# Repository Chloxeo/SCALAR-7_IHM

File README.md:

# SCALAR-7 : IHM Bas

HMI (Human-Machine Interface) board of the **lower stage** of **SCALAR-7**, a two-stage rocket launched at **C'Space 2026**.
It is the external control panel of the lower stage: it switches on, arms and monitors the **sequencer** and the **experiment** boards, and gives access to their debug ports without opening the rocket.

---
## Table of contents

- [Board features](#board-features)
- [Architecture](#architecture)
  - [Sequencer side](#sequencer-side)
  - [Experiment side](#experiment-side)
- [Main components](#main-components)
- [Repository structure](#repository-structure)

---

## Board features

| Function | Sequencer side | Experiment side |
|---|---|---|
| Board connection | D-Sub 15 (J2) | D-Sub 15 (J5) |
| Power switch | SPDT switch on the battery line (SW3) | SPDT switch on the battery line (SW4) |
| Arming | Arming jack connector (J1) | Arming jack connector (J4) |
| Status LEDs | 3V3, 5V, 6V, 12V rails + sequencer status | 3V3, 5V rails + experiment status |
| Debug | 6-pin connector for the Pico (SWD, UART, debug supply) (J3) | 6-pin connector for the Pico (SWD, UART, debug supply) (J6) |
| Test buttons | Parachute servo (SW2) and SSIE motor (SW1) | — |

---

## Architecture

```mermaid
flowchart LR
    subgraph SEQ_SIDE[Sequencer side]
        SW3[Power switch] 
        J1[Arming jack]
        LEDS_SEQ[Rail + status LEDs]
        BTN[SSIE / parachute<br/>test buttons]
        DBG_SEQ[Debug connector]
    end
    subgraph EXP_SIDE[Experiment side]
        SW4[Power switch]
        J4[Arming jack]
        LEDS_EXP[Rail + status LEDs]
        DBG_EXP[Debug connector]
    end

    SEQ[Sequencer board] <-- D-Sub 15 --> SEQ_SIDE
    EXP[Experiment board] <-- D-Sub 15 --> EXP_SIDE
```

The board has no microcontroller: it only routes signals and power. It is split into two independent halves, each with its own ground (`GND_SEQ` and `GND_EXP`), so the sequencer and the experiment stay electrically separated.

### Sequencer side

- **Power**: the sequencer's battery comes onto the HMI through the D-Sub connector and goes back through the power switch, which switches the sequencer on.
- **Arming**: the arming jack connector sends its state to a GPIO of the sequencer's Pico.
- **Status**: one LED per supply rail (3V3, 5V, 6V, 12V) and one status LED driven by the sequencer.
- **Tests**: two push buttons trigger the SSIE motor and the parachute servo for ground tests.
- **Debug**: a 6-pin connector gives access to the Pico's SWD, debug UART and debug supply.

### Experiment side

- **Power**: same principle as the sequencer side, with its own power switch.
- **Arming**: the arming jack connector sends its state to a GPIO of the experiment board's Pico.
- **Status**: one LED per supply rail (3V3, 5V) and one status LED driven by the experiment board.
- **Debug**: a 6-pin connector gives access to the Pico's SWD, debug UART and debug supply.

---

## Main components

| Ref. | Component | Function |
|---|---|---|
| J2, J5 | D-Sub 15 | Connection to the sequencer / experiment boards |
| SW3, SW4 | SPDT switches | Power switches |
| J1, J4 | 2-pin connectors | Arming jacks |
| J3, J6 | 6-pin connectors | Pico debug |
| SW1, SW2 | TE 1825910-6 | SSIE and parachute test buttons |
| D1–D8 | LEDs | Rail and status indicators |

---

## Repository structure

```
SCALAR-7_IHM_Bas/
├── hardware/          # KiCad project
├── images/
├── schematic.pdf
└── README.md
```

---

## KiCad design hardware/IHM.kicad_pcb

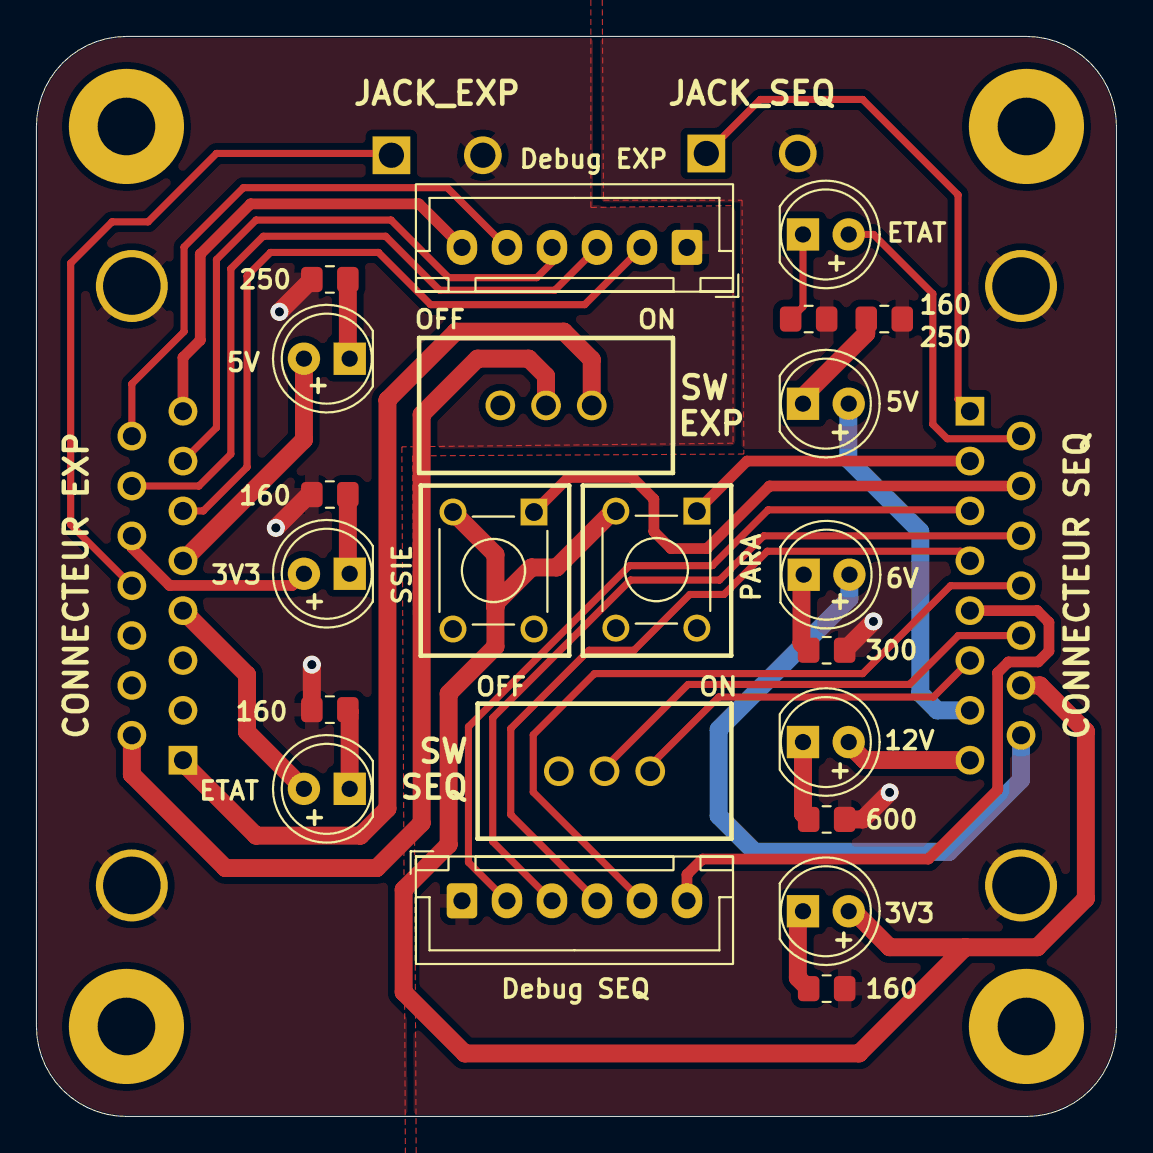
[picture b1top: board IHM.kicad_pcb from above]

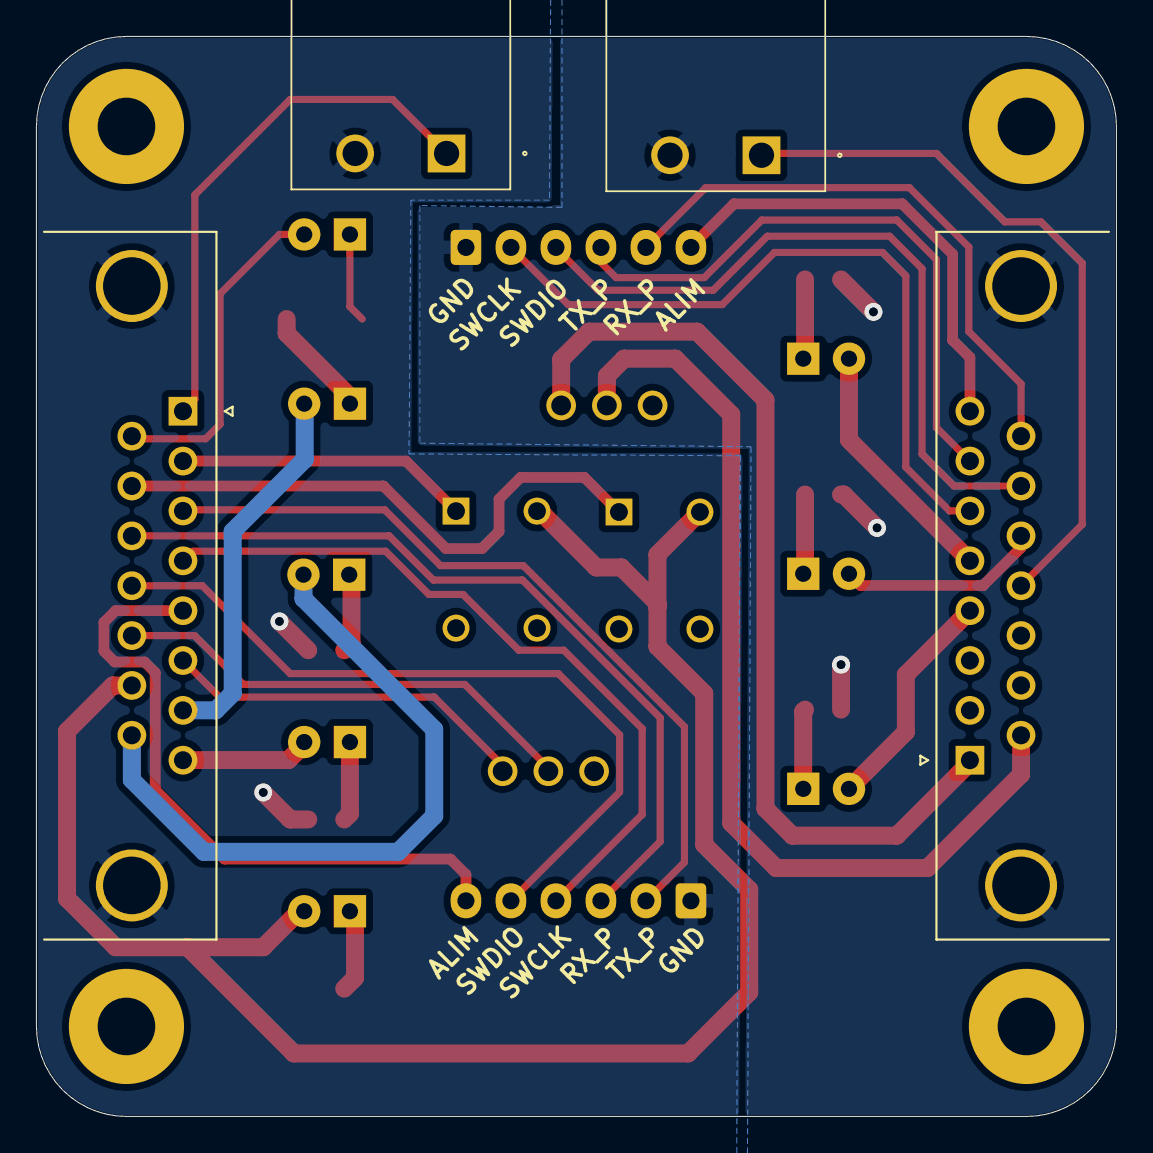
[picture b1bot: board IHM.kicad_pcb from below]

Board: 2 copper layers, 60.0 x 60.0 mm, 30 parts (4 on the bottom side), 36 nets.

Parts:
D1, D2, D3, D4, D5, D6, D7, D8: LED; LED_D5.0mm
H1, H2, H3, H4: MountingHole; MountingHole_3.2mm_M3_Pad
J1: JACK_SEQ; Bornier_Enfichable_2Pin_5mm_Horizontal
J2: CONNECTEUR SEQ; DSUB-15_Pins_Horizontal_P2.77x2.84mm_EdgePinOffset4.94mm_Ho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
J3: Debug SEQ; JST_XH_B6B-XH-A_1x06_P2.50mm_Vertical
J4: JACK_EXP; Bornier_Enfichable_2Pin_5mm_Horizontal
J5: CONNECTEUR EXP; DSUB-15_Pins_Horizontal_P2.77x2.84mm_EdgePinOffset4.94mm_Ho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
J6: Debug EXP; JST_XH_B6B-XH-A_1x06_P2.50mm_Vertical
R1, R5, R6, R8: 160; R_0805_2012Metric_Pad1.20x1.40mm_HandSolder
R2, R7: 250; R_0805_2012Metric_Pad1.20x1.40mm_HandSolder
R3: 300; R_0805_2012Metric_Pad1.20x1.40mm_HandSolder
R4: 600; R_0805_2012Metric_Pad1.20x1.40mm_HandSolder
SW1: SSIE; SW_1825910-6-4
SW2: PARA; SW_1825910-6-4
SW3: SEQ; 25139NAH
SW4: EXP; 25139NAH

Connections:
+3.3V_EXP: D6.2 (A), J5.13
+3.3V_SEQ: D1.2 (A), J2.14, SW1.3, SW2.3
+5V_EXP: D7.2 (A), J5.5
+5V_SEQ: D2.2 (A), J2.7
+6V_SEQ: D3.2 (A), J2.15
+12V_SEQ: D4.2 (A), J2.8
/ALIM_DEBUG_EXP: J5.8, J6.6
/ALIM_DEBUG_SEQ: J2.5, J3.6
/BTN_PARA: J2.2, SW2.1
/BTN_SSIE: J2.10, SW1.1
/ETAT_EXP: D8.2 (A), J5.4
/ETAT_SEQ: D5.2 (A), J2.9
/RX_PROBE_EXP: J5.15, J6.5
/RX_PROBE_SEQ: J2.11 (P111), J3.3
/SWCLK_EXP: J5.6, J6.2
/SWCLK_SEQ: J2.4, J3.4
/SWDIO_EXP: J5.14, J6.3
/SWDIO_SEQ: J2.12, J3.5
/TX_PROBE_EXP: J5.7, J6.4
/TX_PROBE_SEQ: J2.3, J3.2
GND_EXP: J4.2, J5.0 (PAD), J6.1, R6.2, R7.2, R8.2
GND_SEQ: J1.2, J2.0 (PAD), J3.1, R1.2, R2.2, R3.2, R4.2, R5.2
unnamed: D1.1 (K), R1.1
unnamed: D2.1 (K), R2.1
unnamed: D3.1 (K), R3.1
unnamed: D4.1 (K), R4.1
unnamed: D5.1 (K), R5.1
unnamed: D6.1 (K), R6.1
unnamed: D7.1 (K), R7.1
unnamed: D8.1 (K), R8.1
unnamed: J1.1, J2.1
unnamed: J2.13, SW3.2 (B)
unnamed: J4.1, J5.12
unnamed: J5.9, SW4.2 (B)
unnamed: J2.6, SW3.3 (C)
unnamed: J5.1, SW4.3 (C)
